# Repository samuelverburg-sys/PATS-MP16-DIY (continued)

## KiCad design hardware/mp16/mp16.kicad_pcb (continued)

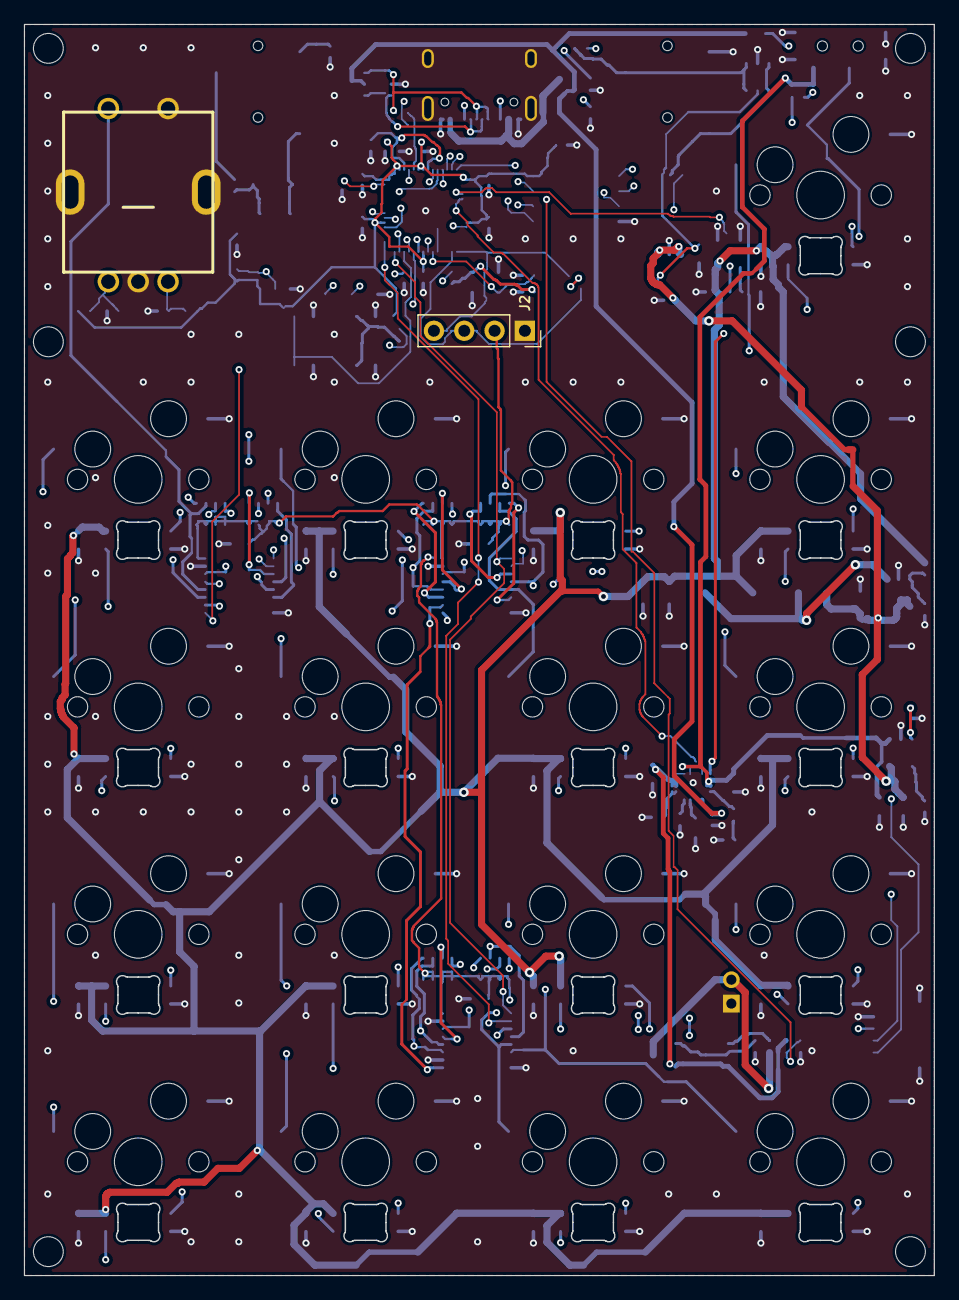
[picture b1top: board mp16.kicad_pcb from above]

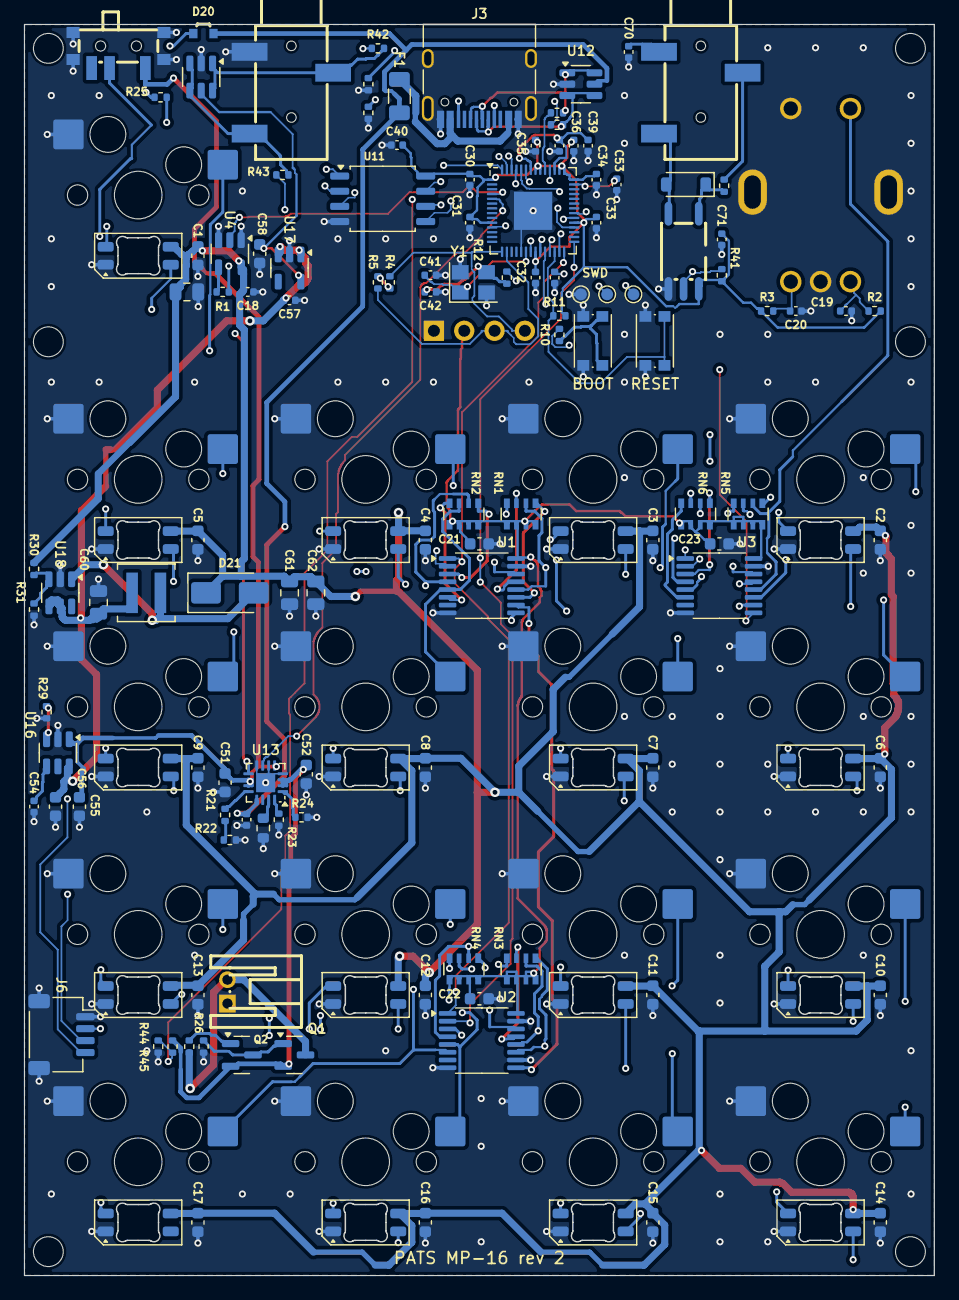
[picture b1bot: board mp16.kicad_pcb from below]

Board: 4 copper layers, 76.2 x 104.8 mm, 160 parts (152 on the bottom side), 104 nets.

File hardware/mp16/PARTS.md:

# PATS MP-16 DIY kit rev 2: parts

Generated from `mp16/design.py` by `tools/parts_table.py`; do not edit by hand.
Check every **unverified** LCSC number in the JLCPCB BOM preview (description, value, package) before ordering.

| Qty | References | Value | Footprint | LCSC | Part | Source of the LCSC number |
|---|---|---|---|---|---|---|
| 1 | SW1 | SHIFT | MX-Hotswap-1U | C41430893 | Kailh CPG151101S11-16 | rev-1 BOM |
| 17 | D1, D2, D3, D4, D5, D6, D7, D8, D9, D10, D11, D12, D13, D14, D15, D16, D17 | SK6812MINI-E | LED_SK6812MINI-E_3.2x2.8mm_P1.5mm_ReverseMount | C5149201 | SK6812MINI-E | Samuel (PATS BOM exports) |
| 20 | C1, C2, C3, C4, C5, C6, C7, C8, C9, C10, C11, C12, C13, C14, C15, C16, C17, C21, C22, C23 | 100n | C_0603_1608Metric | C14663 |  | PATS checked list |
| 1 | SW2 | P1 | MX-Hotswap-1U | C41430893 | Kailh CPG151101S11-16 | rev-1 BOM |
| 1 | SW3 | P2 | MX-Hotswap-1U | C41430893 | Kailh CPG151101S11-16 | rev-1 BOM |
| 1 | SW4 | P3 | MX-Hotswap-1U | C41430893 | Kailh CPG151101S11-16 | rev-1 BOM |
| 1 | SW5 | P4 | MX-Hotswap-1U | C41430893 | Kailh CPG151101S11-16 | rev-1 BOM |
| 1 | SW6 | P5 | MX-Hotswap-1U | C41430893 | Kailh CPG151101S11-16 | rev-1 BOM |
| 1 | SW7 | P6 | MX-Hotswap-1U | C41430893 | Kailh CPG151101S11-16 | rev-1 BOM |
| 1 | SW8 | P7 | MX-Hotswap-1U | C41430893 | Kailh CPG151101S11-16 | rev-1 BOM |
| 1 | SW9 | P8 | MX-Hotswap-1U | C41430893 | Kailh CPG151101S11-16 | rev-1 BOM |
| 1 | SW10 | P9 | MX-Hotswap-1U | C41430893 | Kailh CPG151101S11-16 | rev-1 BOM |
| 1 | SW11 | P10 | MX-Hotswap-1U | C41430893 | Kailh CPG151101S11-16 | rev-1 BOM |
| 1 | SW12 | P11 | MX-Hotswap-1U | C41430893 | Kailh CPG151101S11-16 | rev-1 BOM |
| 1 | SW13 | P12 | MX-Hotswap-1U | C41430893 | Kailh CPG151101S11-16 | rev-1 BOM |
| 1 | SW14 | P13 | MX-Hotswap-1U | C41430893 | Kailh CPG151101S11-16 | rev-1 BOM |
| 1 | SW15 | P14 | MX-Hotswap-1U | C41430893 | Kailh CPG151101S11-16 | rev-1 BOM |
| 1 | SW16 | P15 | MX-Hotswap-1U | C41430893 | Kailh CPG151101S11-16 | rev-1 BOM |
| 1 | SW17 | P16 | MX-Hotswap-1U | C41430893 | Kailh CPG151101S11-16 | rev-1 BOM |
| 1 | U4 | 74AHCT1G125 | SOT-23-5 | C52140417 | 74AHCT1G125GV | Samuel (PATS BOM exports) |
| 2 | R1, R42 | 33 | R_0402_1005Metric | C25105 |  | **unverified** |
| 12 | C18, C30, C31, C32, C33, C34, C35, C38, C39, C40, C53, C71 | 100n | C_0402_1005Metric | C1525 |  | **unverified** |
| 1 | ENC1 | PEC11R 24 PPR + switch | RotaryEncoder_Bourns_PEC11R-4215F-S0024 | C143790 | Bourns PEC11R-4215F-S0024 | rev-1 BOM |
| 5 | R2, R3, R11, R24, R31 | 10k | R_0402_1005Metric | C25744 |  | **unverified** |
| 2 | C19, C20 | 10n | C_0402_1005Metric | C15195 |  | **unverified** |
| 3 | U1, U2, U3 | 74HC165 | TSSOP-16_4.4x5mm_P0.65mm | C80696 | 74HC165PW | PATS checked list |
| 6 | RN1, RN2, RN3, RN4, RN5, RN6 | 4x10k | R_Array_Convex_4x0603 | C29718 | 4D03WGJ0103T5E | PATS checked list |
| 1 | J2 | OLED SSD1306 I2C | PinSocket_1x04_P2.54mm_Vertical | - |  | none: choose a part |
| 2 | R4, R5 | 4.7k | R_0402_1005Metric | C25900 |  | **unverified** |
| 1 | U10 | RP2040 | QFN-56-1EP_7x7mm_P0.4mm_EP3.2x3.2mm | C2040 | RP2040 | **unverified** |
| 4 | C36, C37, C50, C57 | 1u | C_0402_1005Metric | C52923 |  | **unverified** |
| 1 | U11 | W25Q128JV | SOIC-8_5.23x5.23mm_P1.27mm | C97521 | W25Q128JVSIQ | LCSC listing seen 2026-10-22 |
| 3 | R10, R12, R21 | 1k | R_0402_1005Metric | C11702 |  | **unverified** |
| 1 | SW18 | BOOT | SW_Push_1P1T_NO_CK_KMR2 | C72443 | C&K KMR221GLFS | PATS checked list |
| 1 | SW19 | RESET | SW_Push_1P1T_NO_CK_KMR2 | C72443 | C&K KMR221GLFS | PATS checked list |
| 1 | Y1 | 12MHz | Crystal_SMD_3225-4Pin_3.2x2.5mm | C20625731 | Abracon ABM8-272-T3 | LCSC listing seen 2026-10-22 |
| 2 | C41, C42 | 15p | C_0402_1005Metric | C1548 |  | **unverified** |
| 1 | J3 | USB-C | USB_C_Receptacle_HRO_TYPE-C-31-M-12 | C165948 | HRO TYPE-C-31-M-12 | PATS checked list |
| 2 | R13, R14 | 5.1k | R_0402_1005Metric | C25905 |  | **unverified** |
| 1 | F1 | 1.5A hold | Fuse_1206_3216Metric | - | 1206 PTC, 1.5 A hold, 6 V | none: choose a part |
| 2 | U12, U20 | USBLC6-2SC6 | SOT-23-6 | C2687116 | USBLC6-2SC6 | Samuel (PATS BOM exports) |
| 2 | R15, R16 | 27 | R_0402_1005Metric | C25100 |  | **unverified** |
| 1 | U13 | BQ24074 | VQFN-16-1EP_3x3mm_P0.5mm_EP1.6x1.6mm | C2861252 | BQ24074RGTR | Samuel (PATS BOM exports) |
| 5 | C51, C52, C55, C56, C58 | 10u | C_0603_1608Metric | C85713 | CL10A106MP8NNNC | rev-1 BOM |
| 1 | R20 | 3k | R_0402_1005Metric | - |  | none: choose a part |
| 1 | R22 | 180 | R_0402_1005Metric | - |  | none: choose a part |
| 1 | R23 | 4.12k | R_0603_1608Metric | C2960702 |  | Samuel (PATS BOM exports) |
| 1 | D20 | charge | LED_SideView_XL-1606_RD | C965860 | XINGLIGHT XL-1606SURC | rev-1 BOM |
| 1 | R25 | 1.5k | R_0402_1005Metric | C25867 |  | **unverified** |
| 1 | J7 | LiPo 1S (pin 1 = GND, pin 2 = +) | JST_PH_S2B-PH-K-S_Horizontal | C173752 | JST S2B-PH-K-S(LF)(SN) | rev-1 BOM |
| 1 | Q1 | DMG2305UX | SOT-23 | C150470 | DMG2305UX-7 | LCSC listing seen 2026-10-22 |
| 3 | R26, R27, R29 | 100k | R_0402_1005Metric | C25741 |  | **unverified** |
| 1 | Q2 | MMBT3906 | SOT-23 | C2940 | MMBT3906 | **unverified** |
| 2 | R44, R45 | 1M | R_0402_1005Metric | C26083 |  | **unverified** |
| 1 | SW20 | Power | SW_SPDT_MK-12C02-G015 | C2911519 | G-Switch MK-12C02-G015 | rev-1 BOM |
| 1 | U16 | TPS22917 | SOT-23-6 | C2681320 | TPS22917DBVR | PATS checked list |
| 1 | C54 | 1n | C_0402_1005Metric | C1523 |  | **unverified** |
| 1 | U17 | AP2112K-3.3 | SOT-23-5 | C51118 | AP2112K-3.3TRG1 | PATS checked list |
| 1 | U18 | MT3608 | SOT-23-6 | C84817 | MT3608 | PATS checked list |
| 4 | C24, C60, C61, C62 | 22u | C_0805_2012Metric | C45783 |  | PATS checked list |
| 1 | L1 | 10uH | L_Coilcraft_XAL4040-XXX | C5144883 | XAL4040-103MEC | PATS checked list |
| 1 | D21 | SS34 | D_SMA | C8678 | SS34 | PATS checked list |
| 1 | R30 | 75k | R_0402_1005Metric | - |  | none: choose a part |
| 1 | J4 | MIDI IN | Jack_3.5mm_PJ-320-3P-SMT | C17701688 | PJ-320-3P SMT | rev-1 BOM |
| 1 | C70 | 100p | C_0402_1005Metric | C1546 |  | **unverified** |
| 1 | R40 | 220 | R_0402_1005Metric | C25091 |  | **unverified** |
| 1 | D22 | 1N4148W | D_SOD-123 | C81598 | 1N4148W | **unverified** |
| 1 | U19 | TLP109 | Toshiba_SO6-5P_TLP109 | C406798 | TLP109(TPL,E | rev-1 BOM |
| 1 | R41 | 2.2k | R_0402_1005Metric | C25879 |  | **unverified** |
| 1 | J5 | MIDI OUT | Jack_3.5mm_PJ-320-3P-SMT | C17701688 | PJ-320-3P SMT | rev-1 BOM |
| 1 | R43 | 10 | R_0402_1005Metric | C25077 |  | **unverified** |
| 1 | J6 | I2C (Qwiic) | JST_SH_SM04B-SRSS-TB_1x04-1MP_P1.00mm_Horizontal | C160404 | JST SM04B-SRSS-TB(LF)(SN) | **unverified** |

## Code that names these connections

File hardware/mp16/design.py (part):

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        (lx, ly), 0, 'B', block='leds', mpn='SK6812MINI-E', lcsc='C5149201')
    cap(f'C{i + 1}', '100n', 'VLED', 'GND', (lx - 5.0, ly), 90, block='leds', lcsc='C14663')

# LED data: 3.3 V from GPIO2 -> 74AHCT1G125 powered from VLED (5 V) -> 33 R -> Shift's LED.
add('U4', '74xGxx:74AHCT1G125', 'Package_TO_SOT_SMD:SOT-23-5', '74AHCT1G125',
    {'1': 'GND', '2': 'LED_DATA', '3': 'GND', '4': 'LED_DRV', '5': 'VLED'}, (59.0, 19.2), 90, 'B',
    block='leds', mpn='74AHCT1G125GV', lcsc='C52140417', note='3.3 V -> 5 V level shifter for the LED data line')
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# Switch inputs: 3x 74HC165 (TSSOP-16), each next to the keys it reads.
#   U1: pads 1-8, between key rows 1 and 2.   U2: pads 9-16, between rows 3 and 4.
#   U3: Shift, encoder push, 6 spares; between key rows 1 and 2 left of U1. (It started next to the
#   RP2040; there it walled in the RP2040's GPIO16-29 side: route 2 left SR_*, EXP_*, ENC_*, RUN open.)
# Chain: U2 Q7 -> U1 DS, U1 Q7 -> U3 DS, U3 Q7 -> SR_DATA (GPIO16). U2 DS = GND.
# Bits read (first = bit 23): U3 D7..D0, U1 D7..D0, U2 D7..D0 (board_pins.h, kSrPadBit).
# ---------------------------------------------------------------------------
sr_inputs = {
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rn = 1
for k, (ref, ((ux, uy), urot, cxy, rn_xy, rn_rot)) in enumerate(SR_PLACE.items()):
    q7, ds = chain[ref]
    pins = {'1': 'SR_LOAD', '2': 'SR_CLK', '7': None, '8': 'GND', '9': q7, '10': ds, '15': 'GND', '16': '+3V3'}
    for i, net in enumerate(sr_inputs[ref]):
        pins[d_pins[f'D{i}']] = net
    add(ref, '74xx:74HC165', 'Package_SO:TSSOP-16_4.4x5mm_P0.65mm', '74HC165', pins, (ux, uy), urot, 'B',
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# ---------------------------------------------------------------------------
# RP2040 (QFN-56, 0.4 mm), W25Q128JV flash, 12 MHz crystal: the Raspberry Pi minimal design
# ("Hardware design with RP2040", Raspberry Pi Ltd). On the bottom the footprint is mirrored: seen from
# above, GPIO0-11 face right, GPIO18-29 left, USB and QSPI up (towards USB-C), crystal and SWD down.
# GPIO allocation: docs/SPEC.md "RP2040 pin allocation" = board_pins.h.
# ---------------------------------------------------------------------------
# Each signal on the side of the chip it leaves towards (seen from above the RP2040 on the bottom is
# mirrored: GPIO0-11 face right, 12-17 down, 18-29 left). Route 2-layer A (2026-11-03) left MIDI_RX, ENC_A/B
# and PGOOD_N open: they had to wrap around the chip. MIDI on UART1 (TX GP8, RX GP21), I2C0 on GP12/13.
GPIO = {
    0: None, 1: None, 2: 'LED_DATA', 3: 'PGOOD_N', 4: None, 5: None, 6: None, 7: None,
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# (pins 46, 47) and nothing above the QSPI pins (51-56).
# MCU_SIDE 'F' (trial, 2026-11-03): the RP2040's capacitors, the flash and the crystal on the top side
# under the OLED, so the bottom around the RP2040 is free for its signals (double-sided assembly).
# C36 (VREG_IN, pin 44) left of C37 (VREG_VOUT, pin 45), as their pins (run 18: the other way round boxed pin 45 in).
# R15/R16 turned so their RP2040 pads face pins 46/47, and C39/C36/C37 0.2 mm left of the USB lane (run 22:
# RP_USB_DN had to cross back between C37 and C35, a 0.88 mm gap).
TOP_Y = 10.15  # the row between USB-C (its body ends at y 9.2) and the RP2040
cap0402('C30', '100n', '+3V3', 'GND', (rp_pin(1)[0] + 1.9, rp_pin(1)[1]), 90, block='mcu', note='IOVDD pin 1', side=MCU_SIDE)
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res0402('R11', '10k', 'RUN', '+3V3', (31.4, 24.4), 0, block='mcu')

# 12 MHz crystal, as the Raspberry Pi design: 1 k series on XOUT, 15 pF loads (ABM8-272-T3, CL 10 pF).
# Under the RP2040's right half, below XIN/XOUT (pins 20, 21).
add('Y1', 'Device:Crystal_GND24', 'Crystal:Crystal_SMD_3225-4Pin_3.2x2.5mm', '12MHz',
    {'1': 'XIN', '2': 'GND', '3': 'XTAL_OUT', '4': 'GND'}, (38.6, 21.6), 0, MCU_SIDE, block='mcu',
    mpn='Abracon ABM8-272-T3', lcsc='C20625731', note='12 MHz, CL 10 pF, approved by Abracon for the RP2040')
res0402('R12', '1k', 'XOUT', 'XTAL_OUT', (35.8, rp_pin(21)[1] + 2.2), 90, block='mcu')  # bottom, by pin 21 (on top, XOUT was left open)
cap0402('C41', '15p', 'XIN', 'GND', (42.2, 21.0), 0, block='mcu', side=MCU_SIDE)
cap0402('C42', '15p', 'XTAL_OUT', 'GND', (42.2, 22.4), 0, block='mcu', side=MCU_SIDE)

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BAT_DIV_AT = [(63.8, 85.6), (65.0, 85.6), (26.6, 13.4)]  # R44, R45 beside Q1/Q2; C53 by GPIO29 (pin 41)
BATTERY_PINS = {'1': (59.2, 82.0), '2': (59.2, 80.0)}  # rev-1 orientation: body to the left of the pins
add('J7', 'Connector_Generic:Conn_01x02', 'PATS:JST_PH_S2B-PH-K-S_Horizontal',
    'LiPo 1S (pin 1 = GND, pin 2 = +)', {'1': 'GND', '2': 'BATT_P'}, side='B', block='power',
    pin_targets=BATTERY_PINS, mpn='JST S2B-PH-K-S(LF)(SN)', lcsc='C173752',
    note='rev-1 part and pinout; through-hole; between keys 11 and 12 (moved from the top band, Samuel ok)')
add('Q1', 'Device:Q_PMOS_GSD', 'Package_TO_SOT_SMD:SOT-23', 'DMG2305UX', {'1': 'Q1_G', '2': 'VBAT', '3': 'BATT_P'},
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# (core/battery.h); charging = USB present (/PGOOD) and not full.
res0402('R44', '1M', 'VBAT', 'BAT_SENSE', BAT_DIV_AT[0], 90, block='power', note='battery divider, top')
res0402('R45', '1M', 'BAT_SENSE', 'GND', BAT_DIV_AT[1], 90, block='power', note='battery divider, bottom')
cap0402('C53', '100n', 'BAT_SENSE', 'GND', BAT_DIV_AT[2], 90, block='power', note='at the ADC pin')

# On/off: slide switch at the rev-1 position -> TPS22917 load switch -> VSW. Charging works with the
# switch off; everything after the load switch (RP2040, LEDs, OLED) is off with it.
add('SW20', 'Switch:SW_SPDT', 'PATS:SW_SPDT_MK-12C02-G015', 'Power',
    {'1': 'VSYS', '2': 'PWR_ON', '3': None}, side='B', block='power', pin_targets=REV1['POWER_SWITCH'],
    mpn='G-Switch MK-12C02-G015', lcsc='C2911519', extra_pads={'SH': 'GND'},
    note='rev-1 part and position (enclosure slot at x 66.8)')
res0402('R29', '100k', 'PWR_ON', 'GND', (74.35, 57.6), 90, block='power')  # above pin 3 (PWR_ON)
add('U16', 'Power_Management:TPS22917DBV', 'Package_TO_SOT_SMD:SOT-23-6', 'TPS22917',
    {'1': 'VSYS', '6': 'VSW', '3': 'PWR_ON', '4': 'CT', '5': None, '2': 'GND'},
    (73.4, 61.0), 90, 'B', block='power', mpn='TPS22917DBVR', lcsc='C2681320', note='2 A load switch')
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NETCLASSES = {
    # The RP2040's 0.4 mm-pitch pins: 0.15 mm tracks.
    'Fine': (0.15, sorted({n for n in rp.values() if n} - {'GND', '+3V3', 'VDD_CORE'})),
    'Medium': (0.4, ['VBUS', 'VSYS', 'VBAT']),  # the BQ24074's 0.5 mm-pitch power pins
    'Usb': (0.2, ['USB_DP', 'USB_DN']),
    'Supply': (0.2, ['+3V3', 'VDD_CORE']),
    'Ground': (0.3, ['GND']),
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    ('all', ['Fine', 'Medium', 'Usb', 'Supply', 'Power', 'Default']),
]
ROUTE_PARALLEL = 3  # three Freerouting runs at once (margins 0.02, 0, 0.04 mm), best kept by KiCad's count
ROUTE_PASSES = 10  # passes per Freerouting run: it returns to its best result by pass 8 and then repeats
ROUTE_TIMEOUT = 1500  # s per Freerouting run; 4 layers took 55-130 s per pass (run 14 timed out at 900)
ROUTE_PROMOTE = {'escape': 1, '*': 0}
OUTER_ONLY_CLASSES = ['Medium', 'Power']  # run 23: power on the outer layers (inner layers are thinner copper)
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PREROUTE_FIRST = ['USB_DP', 'USB_DN', 'RP_USB_DP', 'RP_USB_DN',  # USB: J3 -> ESD -> 27R -> RP2040
                  'XIN', 'XOUT', 'XTAL_OUT',                    # crystal
                  'ISET', 'ITERM']                              # charger current setting
# Not VDD_CORE (run 18): pre-routed across the RP2040 its path wound over the top layer above the top pin row,
# with vias inside the pin ring, and walled in QSPI_SD0/SD1 and +3V3 (open even when routed first, alone).
# Not PGOOD_N (charger /PGOOD -> GPIO3, ~50 mm): pre-routed with its own 60 mm reach it cost 6-11 open
# connections elsewhere (run 7, ROUTING-LOG.md). A per-net reach is possible: ('NET', mm).
# Not QSPI and VDD_CORE: routed first up to 15 mm, their shortest paths walled in the RP2040's GPIO pins
# (ENC_A, MIDI_RX/TX, PGOOD_N, SWCLK left open, 2026-11-03); Freerouting fits them in fine.
PREROUTE_FIRST_MM = 10.0
PREROUTE_KEEP_INSIDE = ['U10', 'U13']  # no pre-routed copper inside the RP2040's and the charger's pin rings (run 20)
ROUTE_LOG_VARS = {'mcu_side': MCU_SIDE}  # experiment switches recorded with every route run (build.py mp16 log)
PREROUTE_MM = 3.0  # pieces of a net <= 3 mm apart: routed and locked before Freerouting (tools/finish.py prejoin_short)
GND_FANOUT_SIDE = 'BF' if MCU_SIDE == 'F' else 'B'  # top too: the RP2040's capacitors (a top pour island left C33 open)
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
